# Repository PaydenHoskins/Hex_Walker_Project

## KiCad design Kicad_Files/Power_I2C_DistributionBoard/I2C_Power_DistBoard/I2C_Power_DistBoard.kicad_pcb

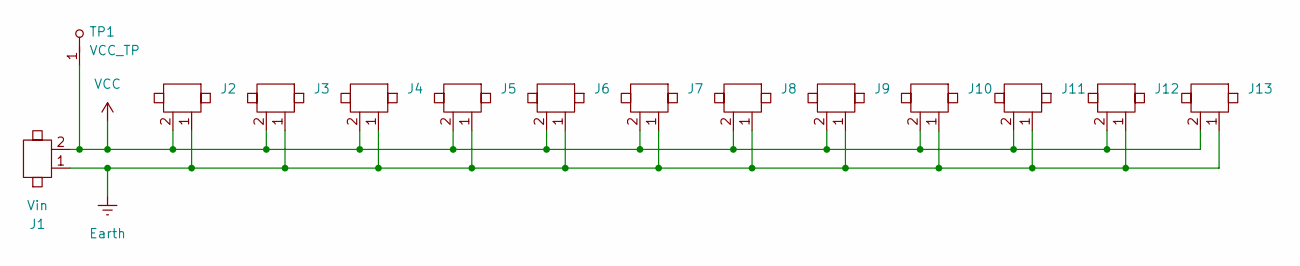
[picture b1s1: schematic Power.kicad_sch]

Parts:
J1: Vin; XT30PW-M_AMA
J2, J3, J4, J5, J6, J7, J8, J9, J10, J11, J12, J13: CONN_XT30PW-F_AMA
TP1: VCC_TP; TP

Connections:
Earth: J1.1, J2.1, J3.1, J4.1, J5.1, J6.1, J7.1, J8.1, J9.1, J10.1, J11.1, J12.1, J13.1; also elsewhere on the board
VCC: J1.2, J2.2, J3.2, J4.2, J5.2, J6.2, J7.2, J8.2, J9.2, J10.2, J11.2, J12.2, J13.2, TP1.1

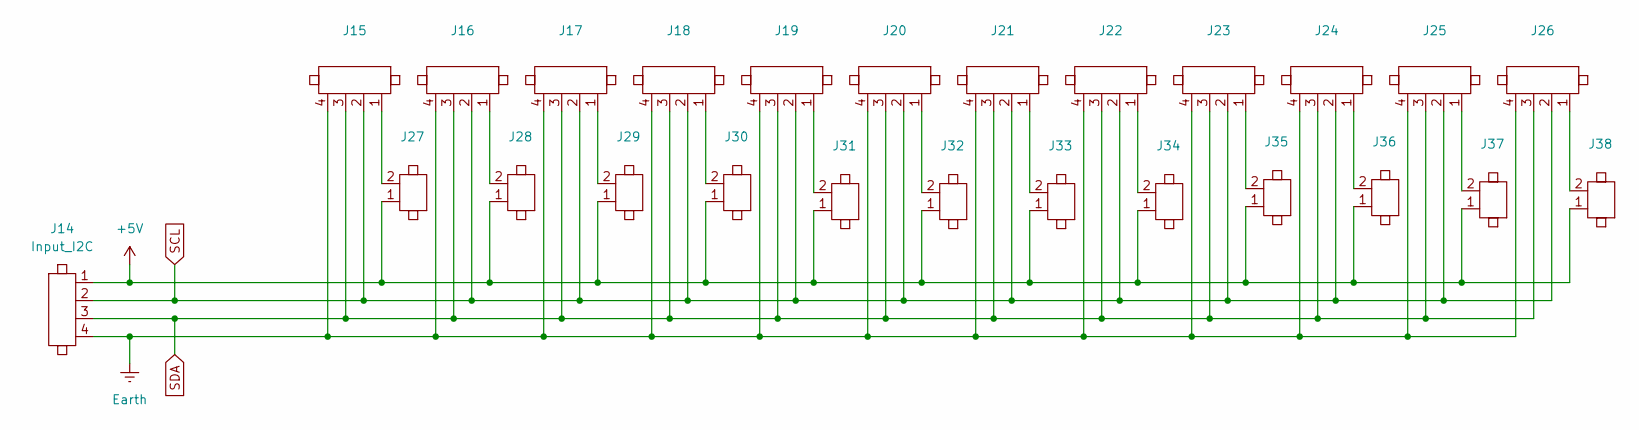
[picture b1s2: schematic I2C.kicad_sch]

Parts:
J14: Input_I2C; Universal Master Rev A I2C B2B
J15, J16, J17, J18, J19, J20, J21, J22, J23, J24, J25, J26: RJ11
J27, J28, J29, J30, J31, J32, J33, J34, J35, J36, J37, J38: Header_1_x_2

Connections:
+5V: J14.1, J27.1, J28.1, J29.1, J30.1, J31.1, J32.1, J33.1, J34.1, J35.1, J36.1, J37.1, J38.1
Earth: J14.4, J15.4, J16.4, J17.4, J18.4, J19.4, J20.4, J21.4, J22.4, J23.4, J24.4, J25.4, J26.4; also elsewhere on the board
unnamed: J15.1, J27.2
unnamed: J16.1, J28.2
unnamed: J17.1, J29.2
unnamed: J18.1, J30.2
unnamed: J19.1, J31.2
unnamed: J20.1, J32.2
unnamed: J21.1, J33.2
unnamed: J22.1, J34.2
unnamed: J23.1, J35.2
unnamed: J24.1, J36.2
unnamed: J25.1, J37.2
unnamed: J26.1, J38.2
SCL: J14.2, J15.2, J16.2, J17.2, J18.2, J19.2, J20.2, J21.2, J22.2, J23.2, J24.2, J25.2, J26.2
SDA: J14.3, J15.3, J16.3, J17.3, J18.3, J19.3, J20.3, J21.3, J22.3, J23.3, J24.3, J25.3, J26.3

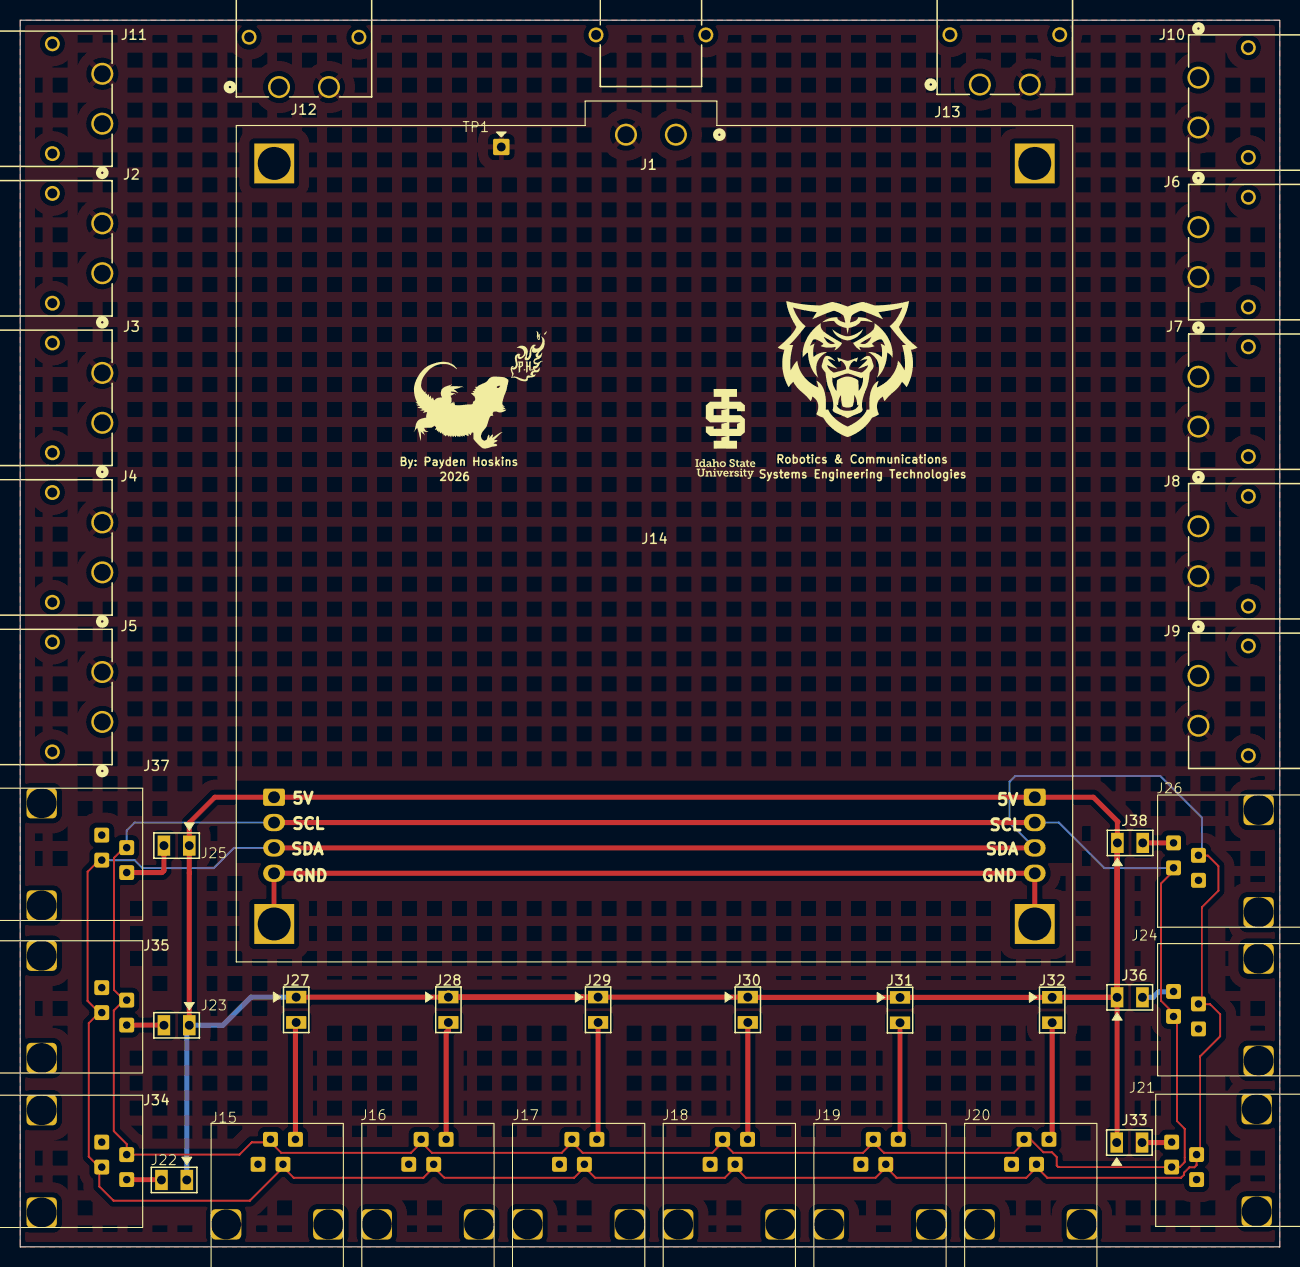
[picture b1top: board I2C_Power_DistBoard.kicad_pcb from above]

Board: 2 copper layers, 126.2 x 122.9 mm, 39 parts (0 on the bottom side), 17 nets.

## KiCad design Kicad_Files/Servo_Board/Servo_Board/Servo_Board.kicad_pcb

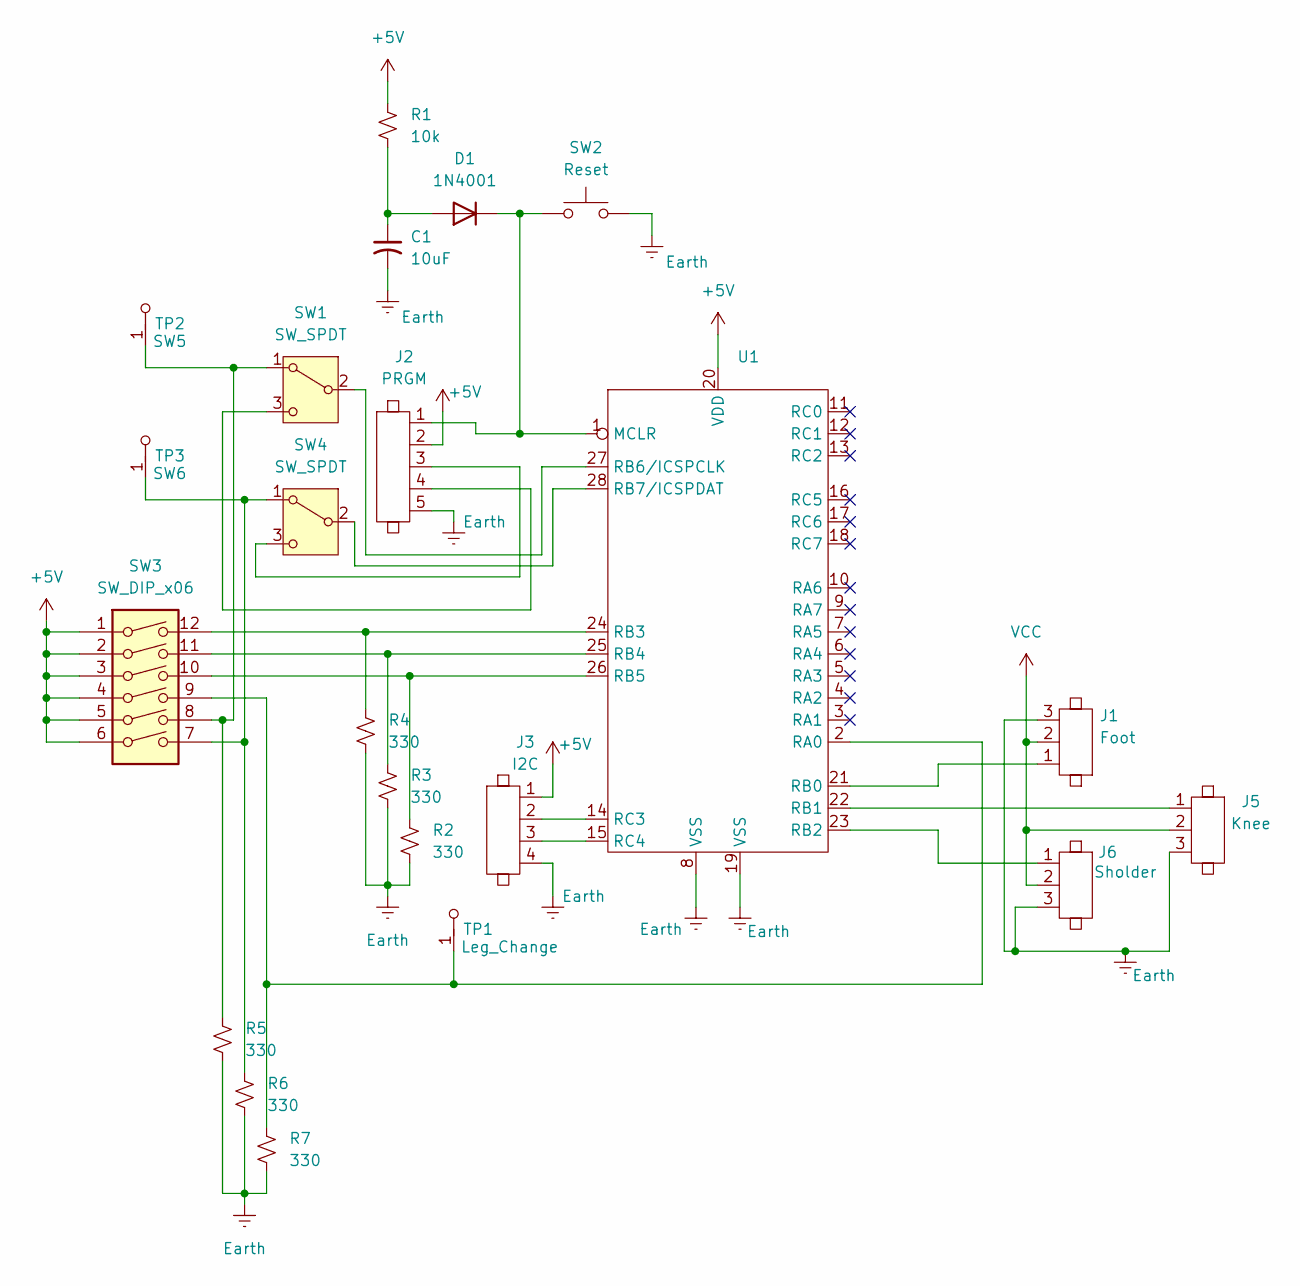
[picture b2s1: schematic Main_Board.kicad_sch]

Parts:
C1: 10uF; 0805
D1: 1N4001; DIODE_0805
J1: Foot; Header_1x03_P2.54mm_Locking
J2: PRGM; Header_1x5
J3: I2C; Header_1x4
J5: Knee; Header_1x03_P2.54mm_Locking
J6: Sholder; Header_1x03_P2.54mm_Locking
R1: 10k; 0805
R2, R3, R4, R5, R6, R7: 330; 0805
SW1, SW4: SW_SPDT; Payden_SW_SPDT_2x0.8mm
SW2: Reset; SW_PUSH_6mm
SW3: SW_DIP_x06; SW_DIP_SPSTx06_Slide_9.78x17.42mm_W7.62mm_P2.54mm
TP1: Leg_Change; TP
TP2: SW5; TP
TP3: SW6; TP
U1: SSOP-28

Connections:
+5V: J2.2, J3.1, R1.1, SW3.1, SW3.2, SW3.3, SW3.4, SW3.5, SW3.6, U1.20 (VDD); also elsewhere on the board
Earth: C1.2, J1.3, J2.5, J3.4, J5.3, J6.3, R2.2, R3.2, R4.2, R5.2, R6.2, R7.2, SW2.2, U1.8 (VSS), U1.19 (VSS); also elsewhere on the board
unnamed: C1.1, D1.2 (A), R1.2
unnamed: D1.1 (K), J2.1, SW2.1, U1.1 (MCLR)
unnamed: R5.1, SW1.1 (A), SW3.8, TP2.1
unnamed: SW1.2 (B), U1.27 (RB6/ICSPCLK)
unnamed: J2.4, SW1.3 (C)
unnamed: R6.1, SW3.7, SW4.1 (A), TP3.1
unnamed: SW4.2 (B), U1.28 (RB7/ICSPDAT)
unnamed: J2.3, SW4.3 (C)
unnamed: R7.1, SW3.9, TP1.1, U1.2 (RA0)
unnamed: J1.1, U1.21 (RB0)
unnamed: J5.1, U1.22 (RB1)
unnamed: J6.1, U1.23 (RB2)
unnamed: R4.1, SW3.12, U1.24 (RB3)
unnamed: R3.1, SW3.11, U1.25 (RB4)
unnamed: R2.1, SW3.10, U1.26 (RB5)
unnamed: J3.2, U1.14 (RC3)
unnamed: J3.3, U1.15 (RC4)
VCC: J1.2, J5.2, J6.2; also elsewhere on the board

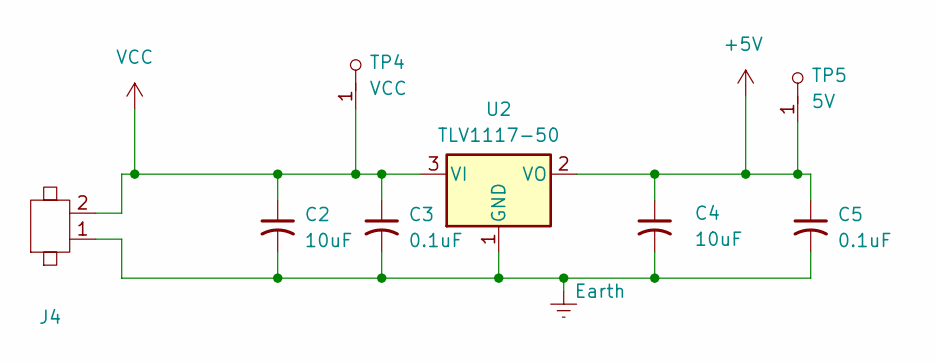
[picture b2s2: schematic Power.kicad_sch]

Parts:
C2, C4: 10uF; 0805
C3, C5: 0.1uF; 0805
J4: XT30PW-M_AMA
TP4: VCC; TP
TP5: 5V; TP
U2: TLV1117-50; Payden_TLV1117-50

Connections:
+5V: C4.1, C5.1, TP5.1, U2.2 (VO); also elsewhere on the board
Earth: C2.2, C3.2, C4.2, C5.2, J4.1, U2.1 (GND); also elsewhere on the board
VCC: C2.1, C3.1, J4.2, TP4.1, U2.3 (VI); also elsewhere on the board

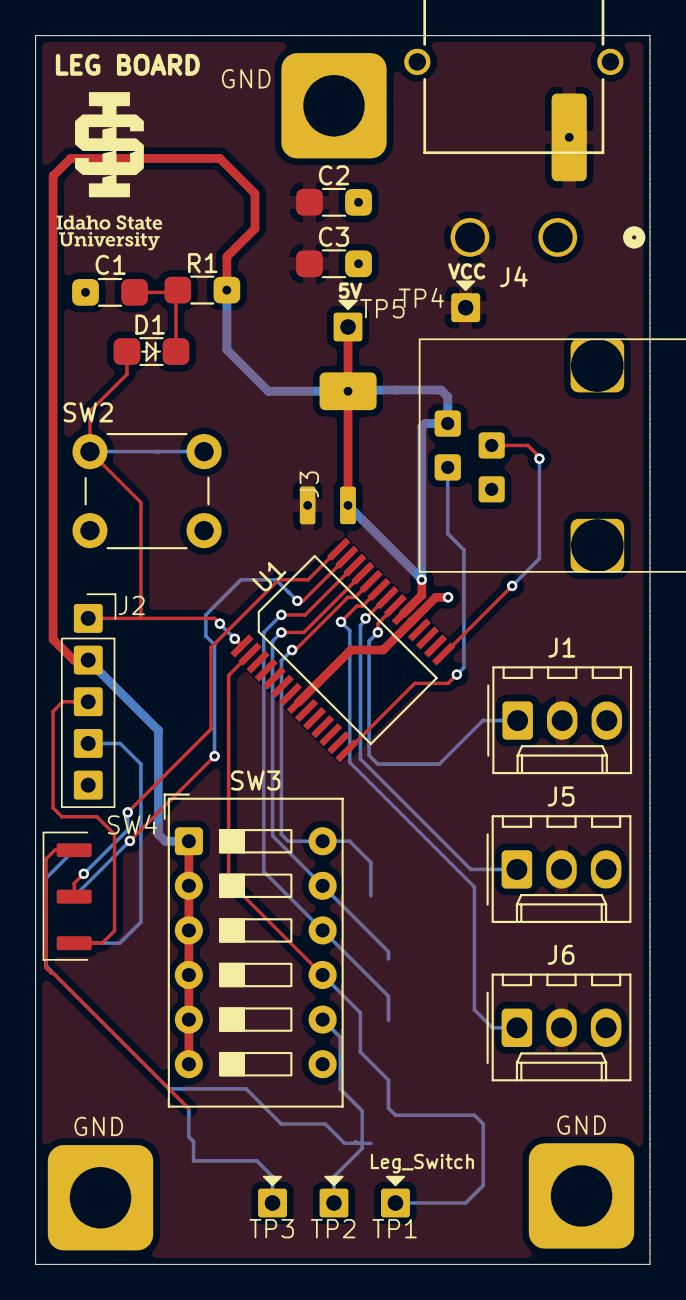
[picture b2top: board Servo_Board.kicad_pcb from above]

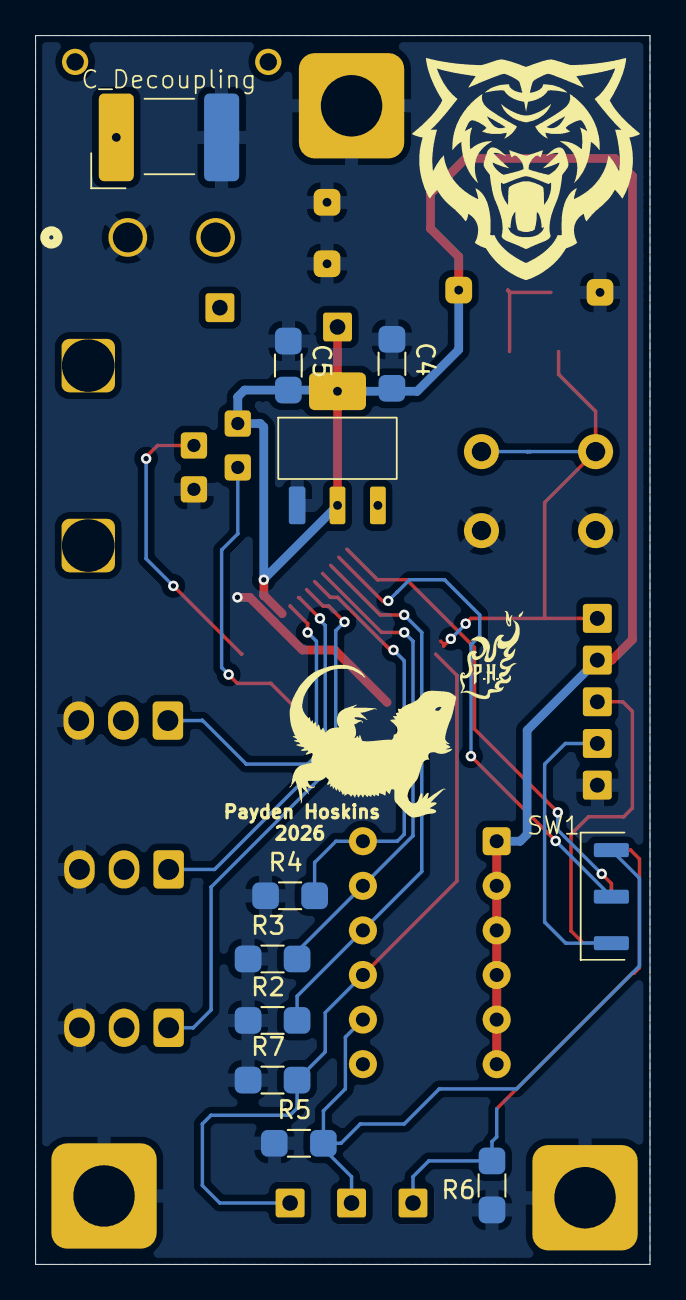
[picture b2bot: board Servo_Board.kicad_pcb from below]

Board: 2 copper layers, 35.0 x 70.0 mm, 34 parts (11 on the bottom side), 20 nets.

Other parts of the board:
C_Decoupling: 25x17
GND: Corner_Pad
GND#2, GND#3: Corner_Pad

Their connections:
Earth: C_Decoupling.2, GND.1, GND#2.1, GND#3.1; also elsewhere on the board
VCC: C_Decoupling.1; also elsewhere on the board

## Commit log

2026-03-18 Universal_Master code, made by Zach. -PH
2026-03-18 Universal_Master_Controller code, made by Zach. -PH
2026-03-18 uses the I2C from the master reciver to act as a easy Master I2C Tester. -PH
2026-03-18 The 3-18-26 version of the servo contoller board, the I2C saves but only byte 2 of the respected addresses saves properly. -PH
2026-03-19 New version of the 03-18-26 code, issue seemes to be the I2C recive gets lost and once it catches up it starts writing the bits in the wrong registers, need to streamline code and determine the best 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
2026-03-19 still dosent work so im going to move onto getting a servo code to move the legs
2026-03-20 got a functioning pwm on a pic to drive a servo. -PH
2026-03-31 code now has all the leg positions but the positions 8 and 9 on legs 1-4-5 seem to get lost and stuck so i need to rework how it determines what legs were selected and when to determine the position 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
2026-03-31 fixed the issue where legs 1,4,5 wold break and then also added a few more positions to make the sequence complete. Now a line of code needs to be added to use a timer to increment the position. -pay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
2026-04-02 remade the positions and added an automatic step process so that i can visually watch both legs work together. Payden H-
2026-04-27 removed file that is no longer used to remove confusion on what is the servo board code. -Payden H
2026-04-27 added all the files for the leg and foot for both 25kg and 80/160kg servos. -Payden H
2026-04-27 added all the Kicad files (these are the updated board that have been fixed since we got the old ones. -Payden H)
2026-04-27 fixed the gitignore file. -Payden H
2026-04-27 Stop tracking .history folders
2026-05-04 Added more photos to the photos folder that pertain to the project, also added new code registers to make tuning of legs easier. -Payden H
2026-05-04 Added more photos to the photos folder.Updated the Universal Receiver to send the servo leg data and made the servo boards read it and change to those positions. The universal master will need to be 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
